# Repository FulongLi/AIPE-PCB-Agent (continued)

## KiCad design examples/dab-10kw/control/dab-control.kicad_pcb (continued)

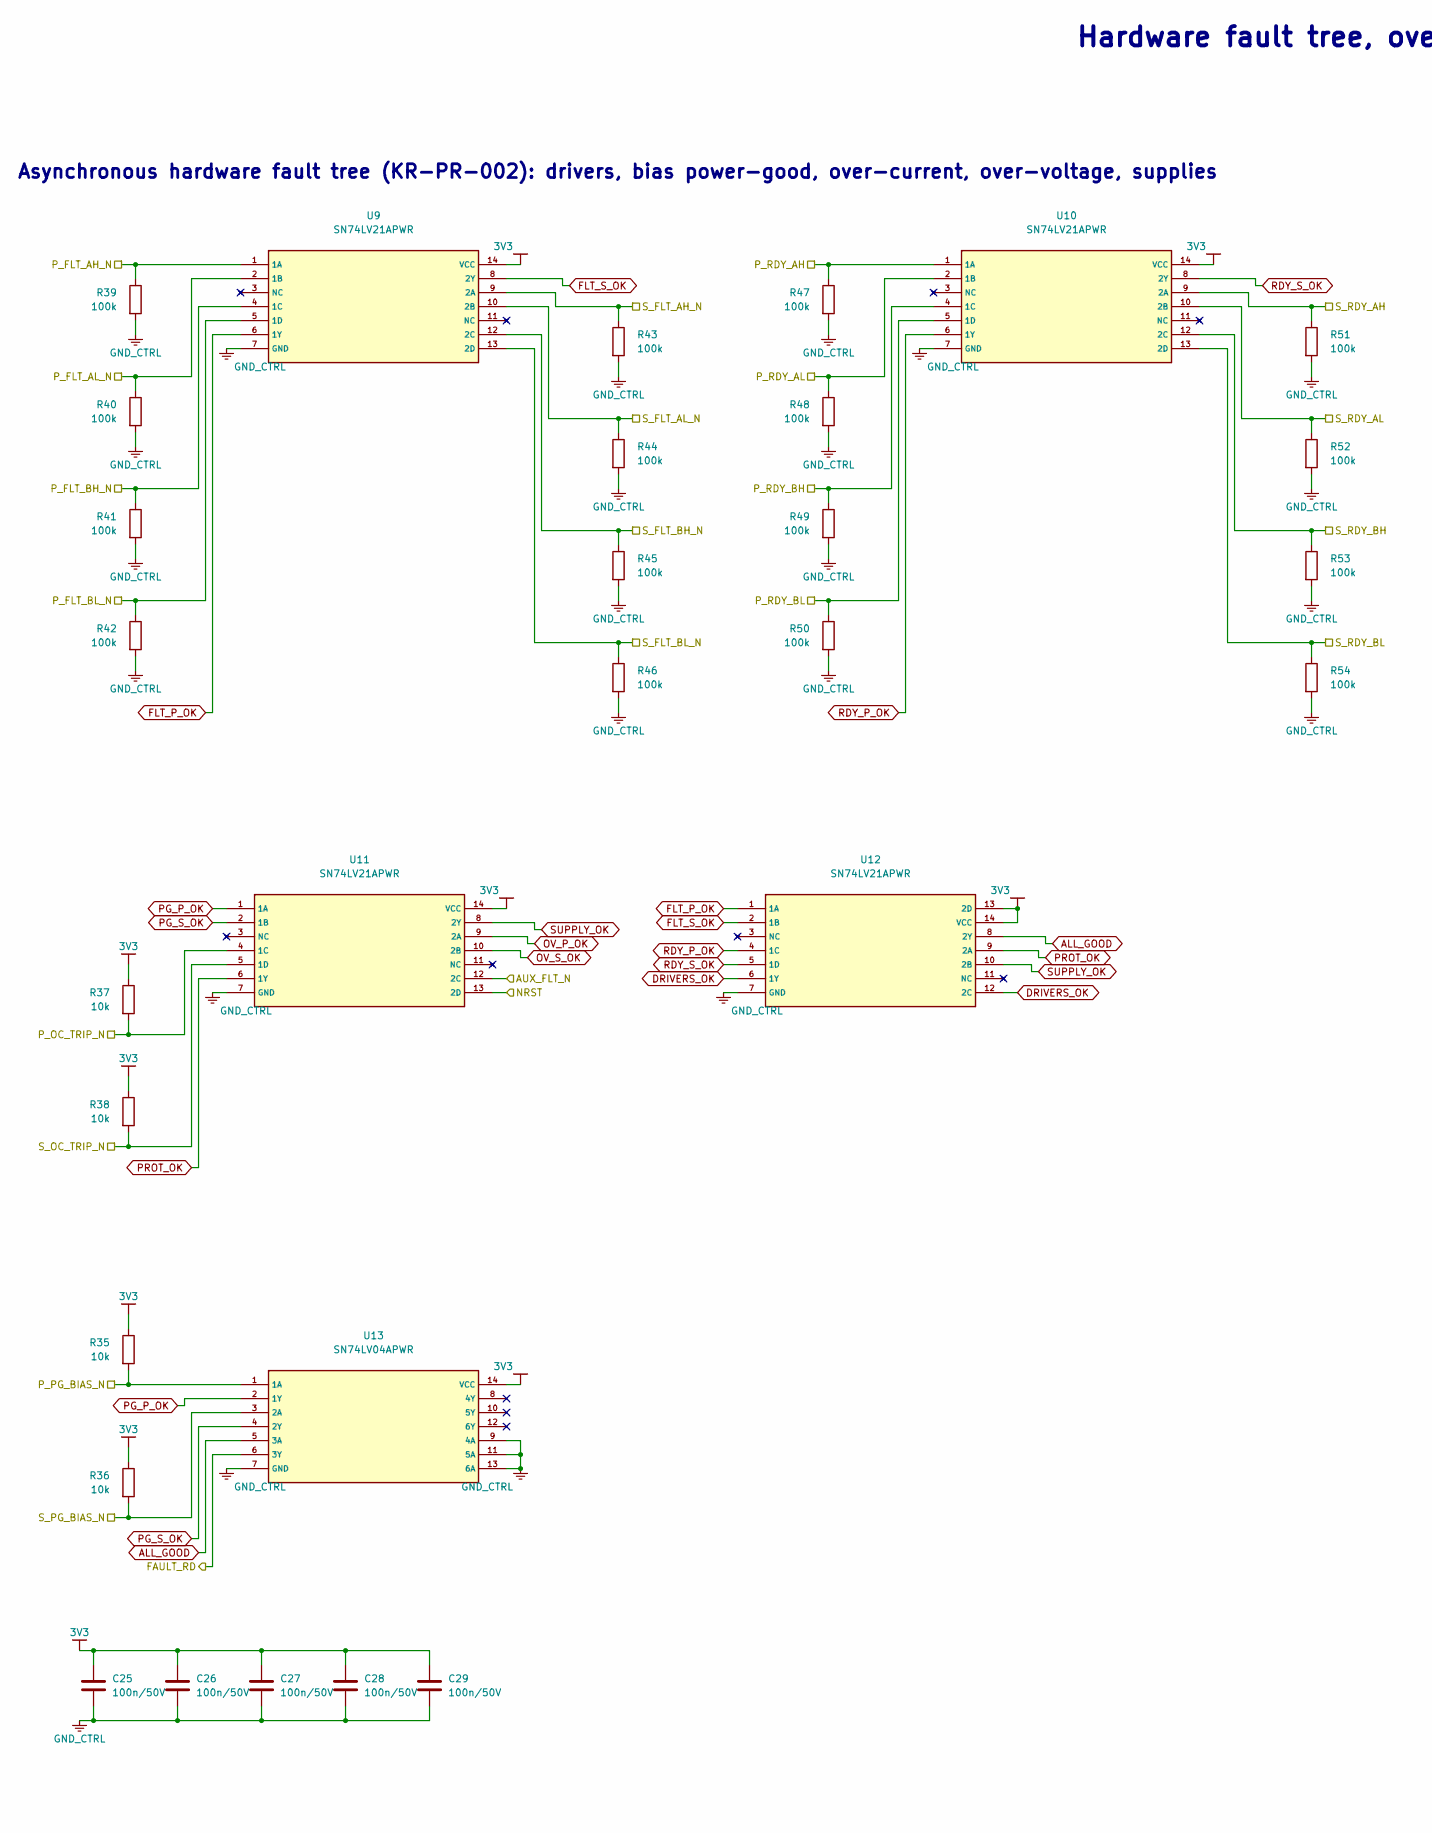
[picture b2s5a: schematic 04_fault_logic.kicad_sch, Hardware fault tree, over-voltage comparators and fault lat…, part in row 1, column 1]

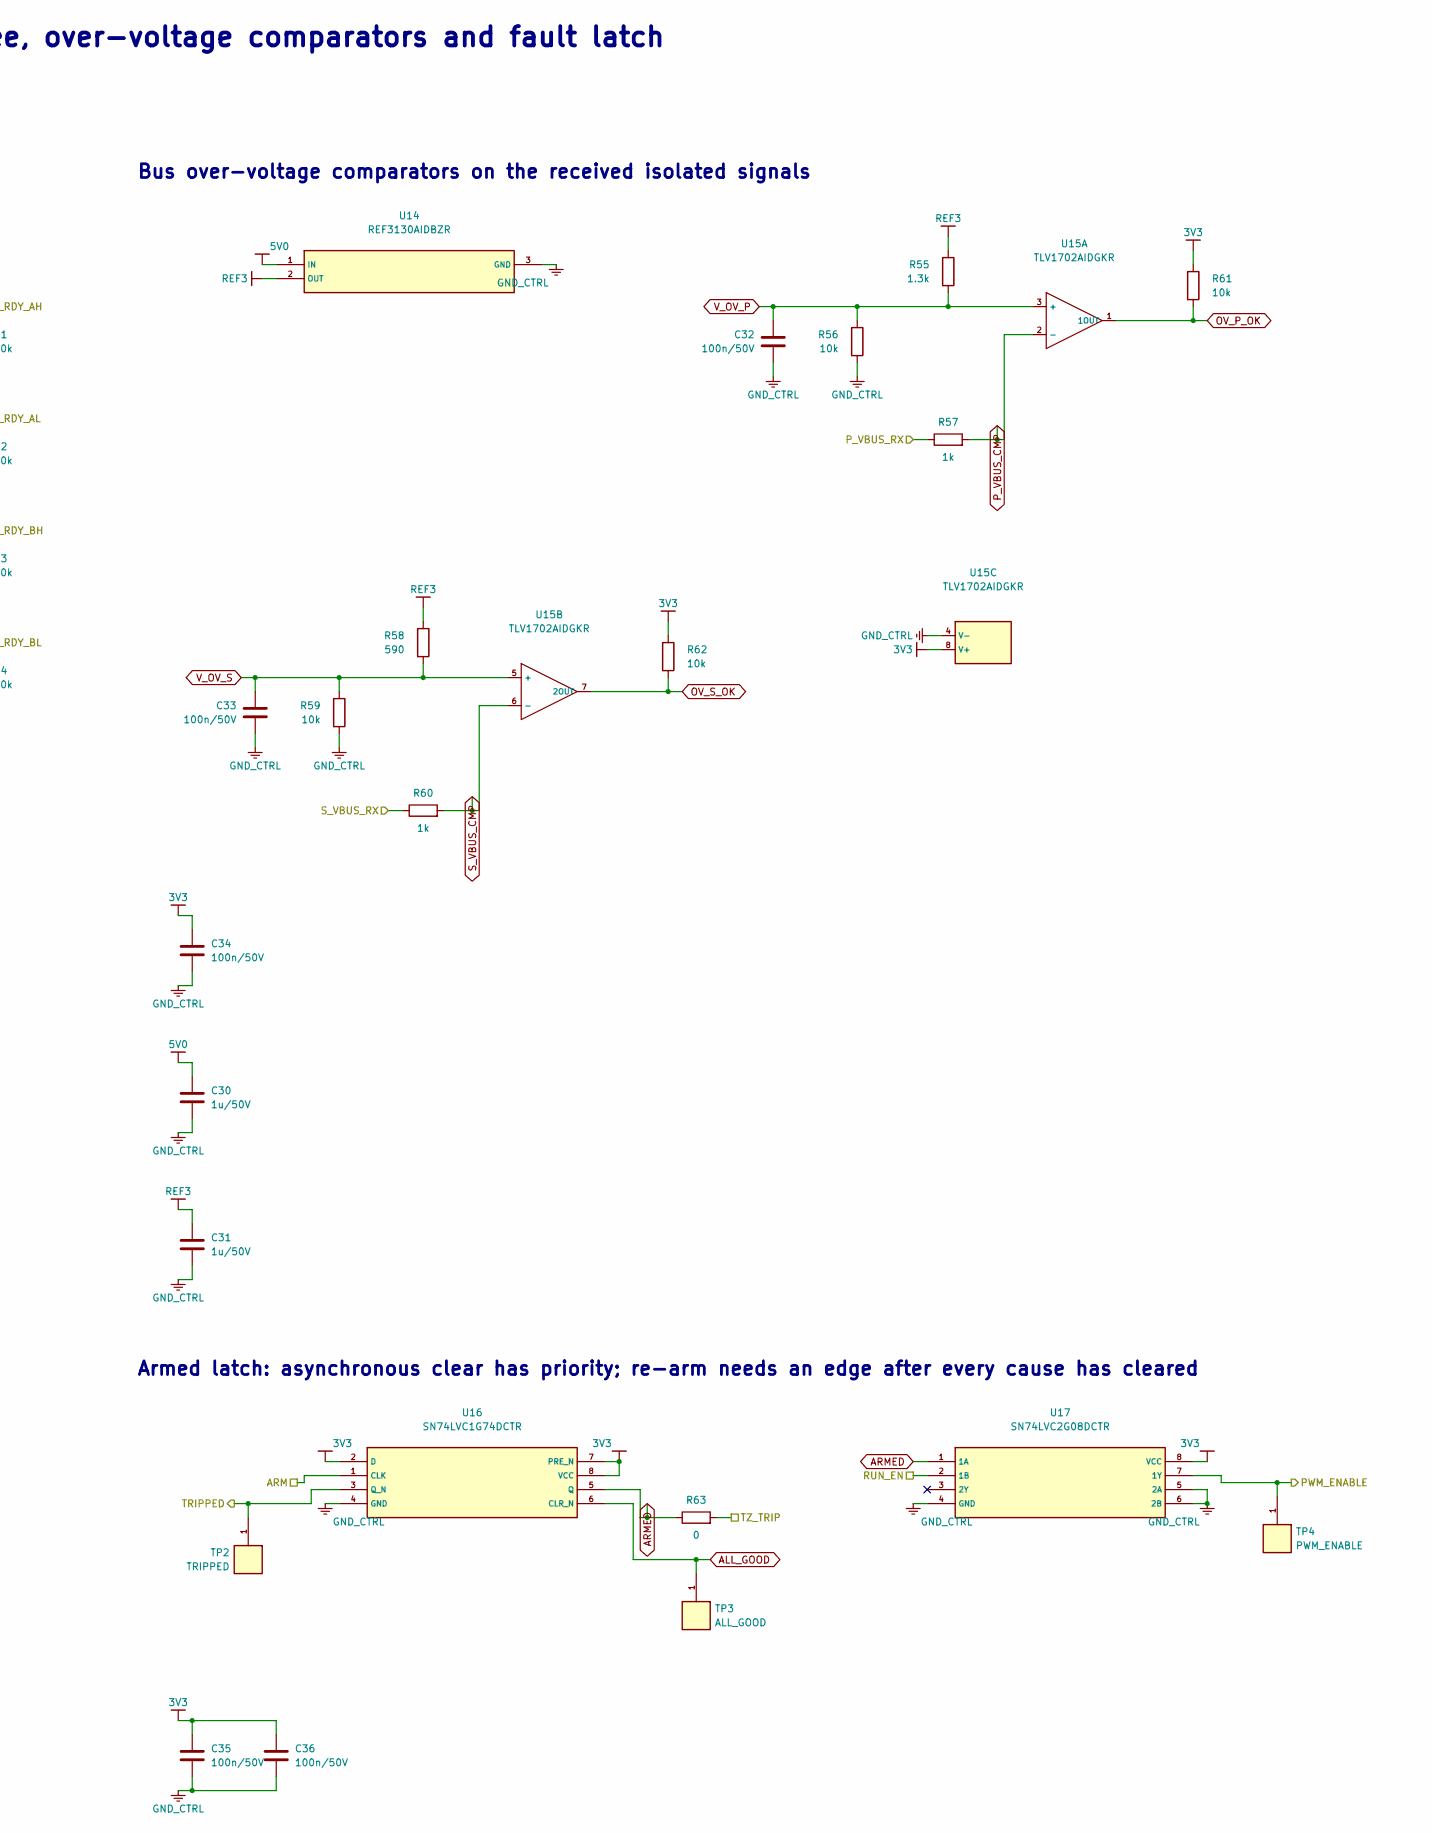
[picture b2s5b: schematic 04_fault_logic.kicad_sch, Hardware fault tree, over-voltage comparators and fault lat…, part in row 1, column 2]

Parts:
C25, C26, C27, C28, C29, C32, C33, C34, C35, C36: 100n/50V; C_0603_1608Metric
C30, C31: 1u/50V; C_0805_2012Metric
R35, R36, R37, R38, R56, R59, R61, R62: 10k; R_0603_1608Metric
R39, R40, R41, R42, R43, R44, R45, R46, R47, R48, R49, R50, R51, R52, R53, R54: 100k; R_0603_1608Metric
R55: 1.3k; R_0603_1608Metric
R57, R60: 1k; R_0603_1608Metric
R58: 590; R_0603_1608Metric
R63: 0; R_0603_1608Metric
TP2: TRIPPED; TestPoint_Pad_D1.0mm
TP3: ALL_GOOD; TestPoint_Pad_D1.0mm
TP4: PWM_ENABLE; TestPoint_Pad_D1.0mm
U9, U10, U11, U12: SN74LV21APWR; TSSOP-14_4.4x5mm_P0.65mm
U13: SN74LV04APWR; TSSOP-14_4.4x5mm_P0.65mm
U14: REF3130AIDBZR; SOT-23
U15: TLV1702AIDGKR; DAB_DGK8
U16: SN74LVC1G74DCTR; SSOP-8_2.95x2.8mm_P0.65mm
U17: SN74LVC2G08DCTR; SSOP-8_2.95x2.8mm_P0.65mm

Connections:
3V3: C25.1, C26.1, C27.1, C28.1, C29.1, C34.1, C35.1, C36.1, R35.1, R36.1, R37.1, R38.1, R61.1, R62.1, U9.14 (VCC), U10.14 (VCC), U11.14 (VCC), U12.13 (2D), U12.14 (VCC), U13.14 (VCC), U15.8 (V+), U16.2 (D), U16.7 (PRE_N), U16.8 (VCC), U17.8 (VCC); also elsewhere on the board
5V0: C30.1, U14.1 (IN); also elsewhere on the board
ALL_GOOD: TP3.1, U12.8 (2Y), U13.5 (3A), U16.6 (CLR_N)
ARM: U16.1 (CLK); also elsewhere on the board
ARMED: R63.1, U16.5 (Q), U17.1 (1A)
AUX_FLT_N: U11.12 (2C); also elsewhere on the board
DRIVERS_OK: U12.6 (1Y), U12.12 (2C)
FAULT_RD: U13.6 (3Y); also elsewhere on the board
FLT_P_OK: U9.6 (1Y), U12.1 (1A)
FLT_S_OK: U9.8 (2Y), U12.2 (1B)
GND_CTRL: C25.2, C26.2, C27.2, C28.2, C29.2, C30.2, C31.2, C32.2, C33.2, C34.2, C35.2, C36.2, R39.2, R40.2, R41.2, R42.2, R43.2, R44.2, R45.2, R46.2, R47.2, R48.2, R49.2, R50.2, R51.2, R52.2, R53.2, R54.2, R56.2, R59.2, U9.7 (GND), U10.7 (GND), U11.7 (GND), U12.7 (GND), U13.7 (GND), U13.9 (4A), U13.11 (5A), U13.13 (6A), U14.3 (GND), U15.4 (V-), U16.4 (GND), U17.4 (GND), U17.5 (2A), U17.6 (2B); also elsewhere on the board
NRST: U11.13 (2D); also elsewhere on the board
OV_P_OK: R61.2, U11.9 (2A), U15.1 (1OUT)
OV_S_OK: R62.2, U11.10 (2B), U15.7 (2OUT)
PG_P_OK: U11.1 (1A), U13.2 (1Y)
PG_S_OK: U11.2 (1B), U13.4 (2Y)
PROT_OK: U11.6 (1Y), U12.9 (2A)
PWM_ENABLE: TP4.1, U17.7 (1Y); also elsewhere on the board
P_FLT_AH_N: R39.1, U9.1 (1A); also elsewhere on the board
P_FLT_AL_N: R40.1, U9.2 (1B); also elsewhere on the board
P_FLT_BH_N: R41.1, U9.4 (1C); also elsewhere on the board
P_FLT_BL_N: R42.1, U9.5 (1D); also elsewhere on the board
P_OC_TRIP_N: R37.2, U11.4 (1C); also elsewhere on the board
P_PG_BIAS_N: R35.2, U13.1 (1A); also elsewhere on the board
P_RDY_AH: R47.1, U10.1 (1A); also elsewhere on the board
P_RDY_AL: R48.1, U10.2 (1B); also elsewhere on the board
P_RDY_BH: R49.1, U10.4 (1C); also elsewhere on the board
P_RDY_BL: R50.1, U10.5 (1D); also elsewhere on the board
P_VBUS_CMP: R57.2, U15.2 (-)
P_VBUS_RX: R57.1; also elsewhere on the board
RDY_P_OK: U10.6 (1Y), U12.4 (1C)
RDY_S_OK: U10.8 (2Y), U12.5 (1D)
REF3: C31.1, R55.1, R58.1, U14.2 (OUT)
RUN_EN: U17.2 (1B); also elsewhere on the board
SUPPLY_OK: U11.8 (2Y), U12.10 (2B)
S_FLT_AH_N: R43.1, U9.9 (2A); also elsewhere on the board
S_FLT_AL_N: R44.1, U9.10 (2B); also elsewhere on the board
S_FLT_BH_N: R45.1, U9.12 (2C); also elsewhere on the board
S_FLT_BL_N: R46.1, U9.13 (2D); also elsewhere on the board
S_OC_TRIP_N: R38.2, U11.5 (1D); also elsewhere on the board
S_PG_BIAS_N: R36.2, U13.3 (2A); also elsewhere on the board
S_RDY_AH: R51.1, U10.9 (2A); also elsewhere on the board
S_RDY_AL: R52.1, U10.10 (2B); also elsewhere on the board
S_RDY_BH: R53.1, U10.12 (2C); also elsewhere on the board
S_RDY_BL: R54.1, U10.13 (2D); also elsewhere on the board
S_VBUS_CMP: R60.2, U15.6 (-)
S_VBUS_RX: R60.1; also elsewhere on the board
TRIPPED: TP2.1, U16.3 (Q_N); also elsewhere on the board
TZ_TRIP: R63.2; also elsewhere on the board
V_OV_P: C32.1, R55.2, R56.1, U15.3 (+)
V_OV_S: C33.1, R58.2, R59.1, U15.5 (+)

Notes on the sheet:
Hardware fault tree, over-voltage comparators and fault latch
Asynchronous hardware fault tree (KR-PR-002): drivers, bias power-good, over-current, over-voltage, supplies
Bus over-voltage comparators on the received isolated signals
Armed latch: asynchronous clear has priority; re-arm needs an edge after every cause has cleared

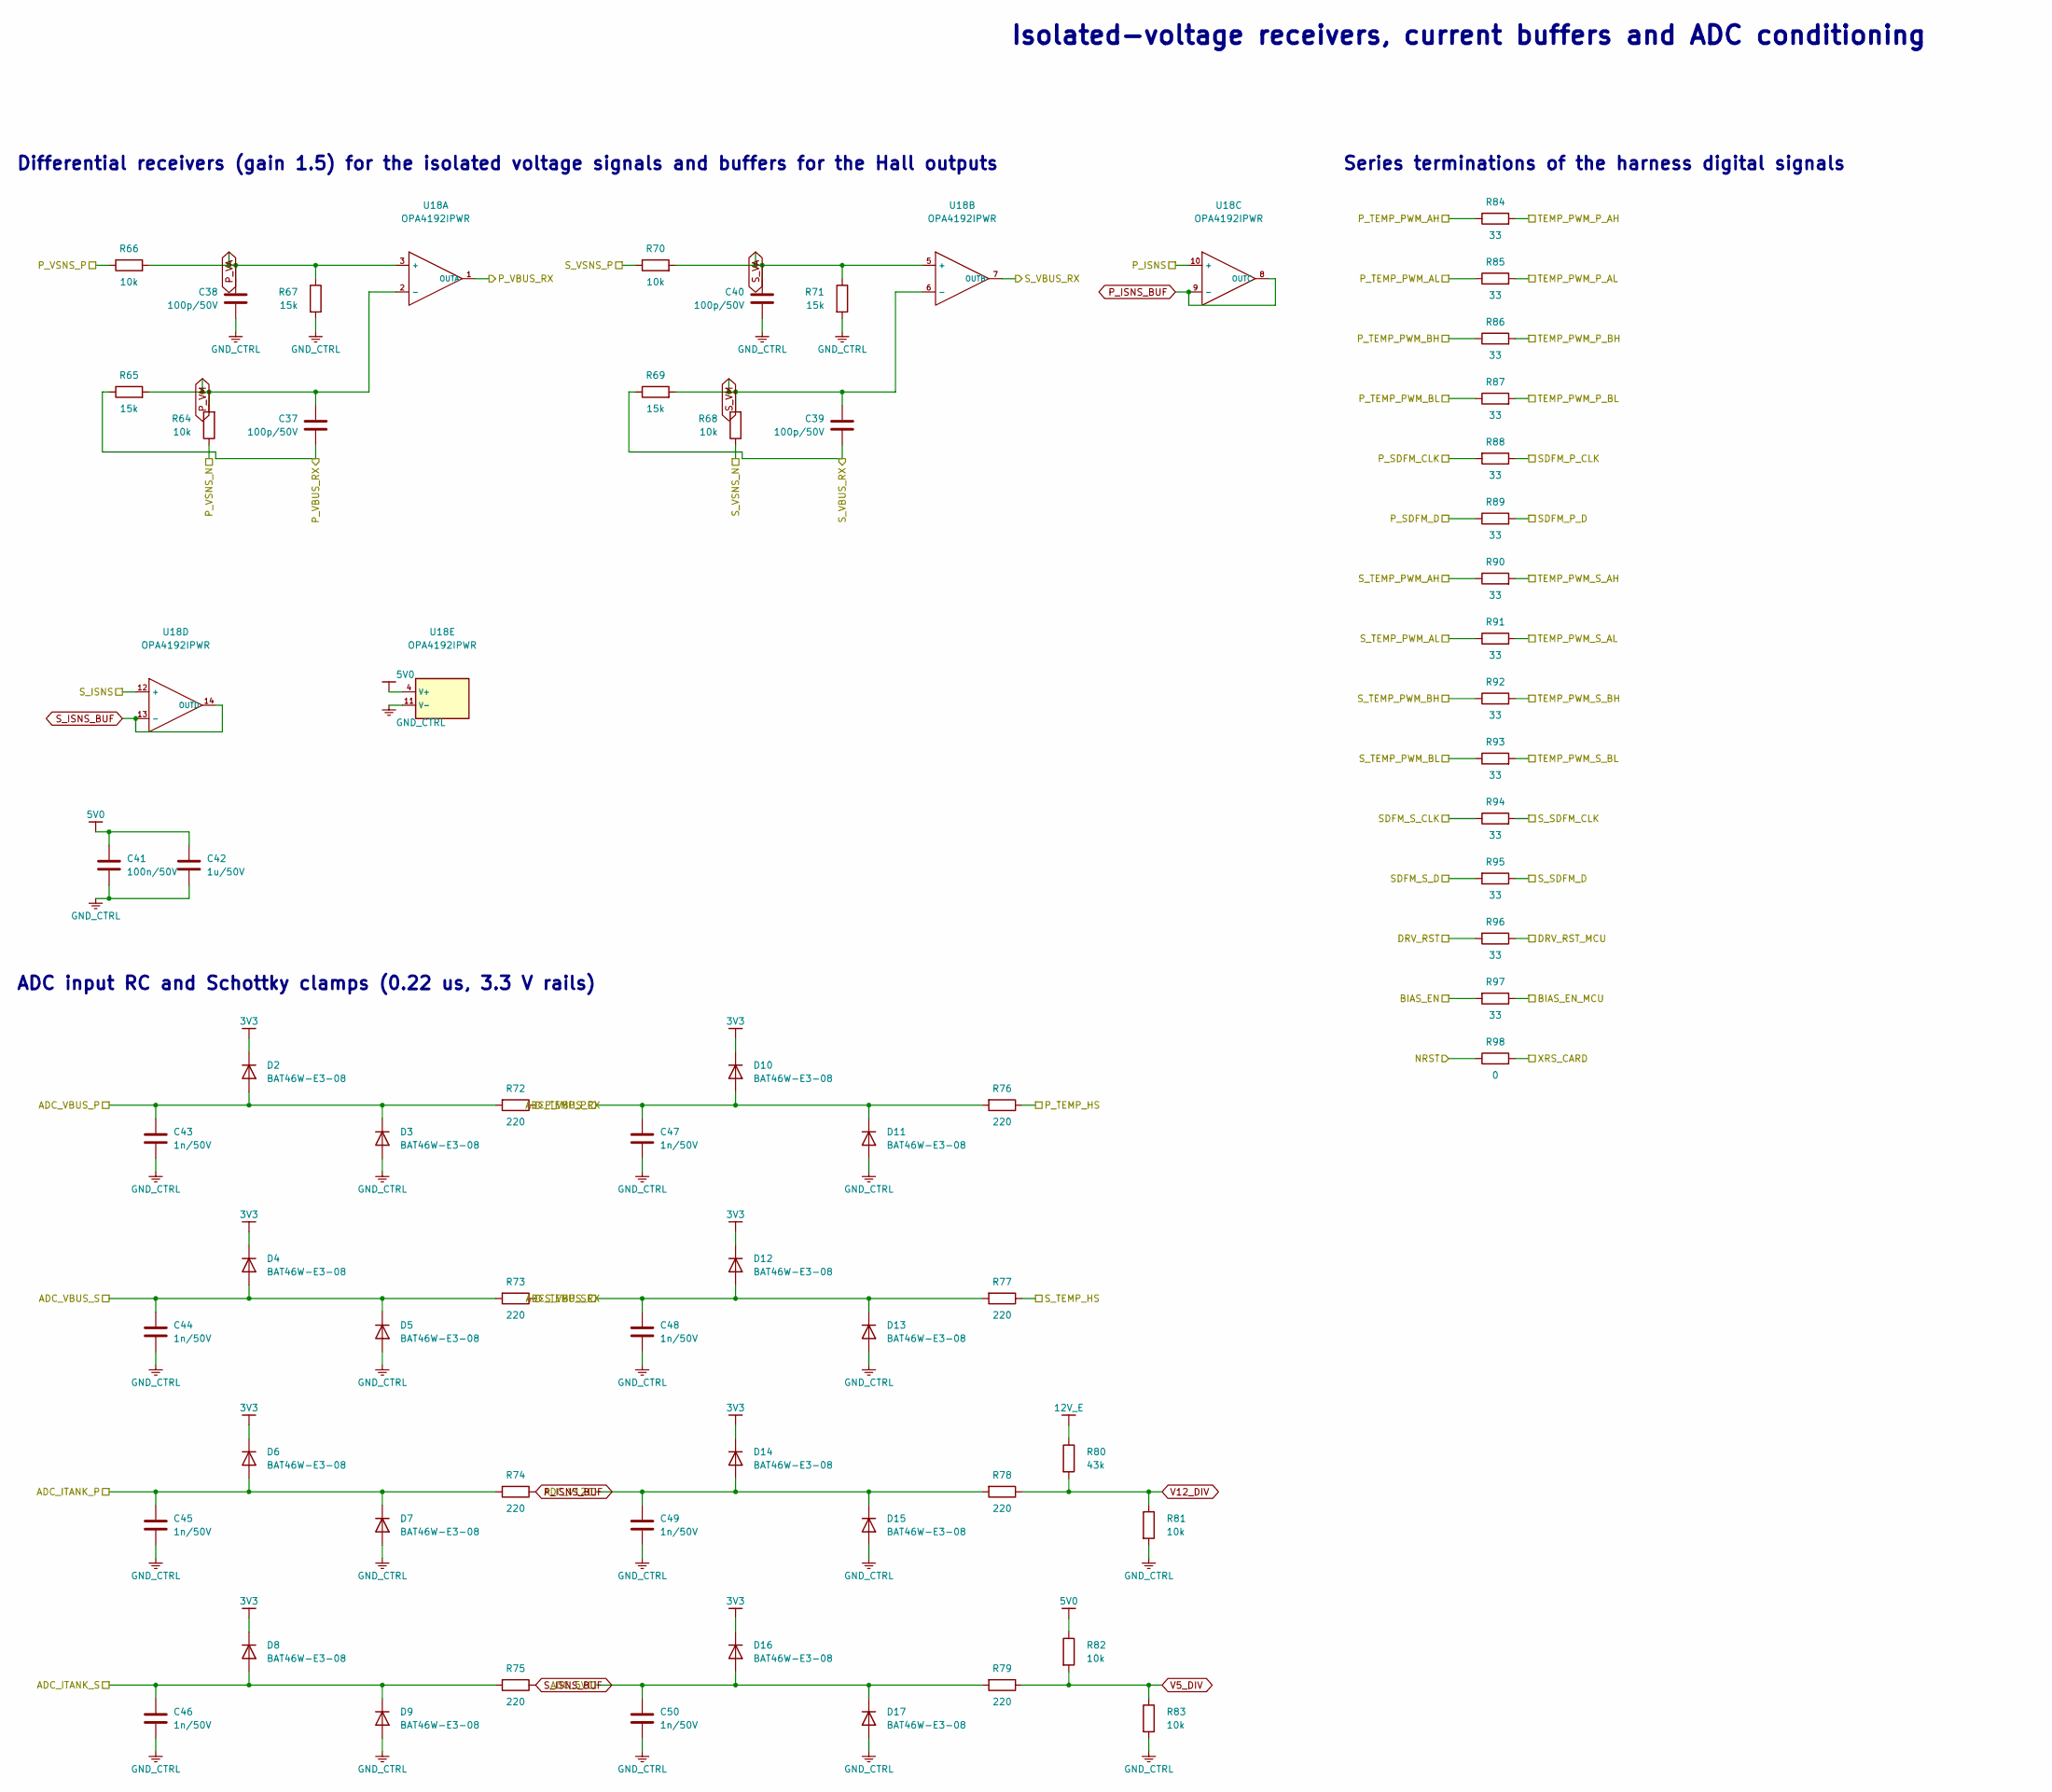
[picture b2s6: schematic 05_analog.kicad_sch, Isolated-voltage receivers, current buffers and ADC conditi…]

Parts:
C37, C38, C39, C40: 100p/50V; C_0603_1608Metric
C41: 100n/50V; C_0603_1608Metric
C42: 1u/50V; C_0805_2012Metric
C43, C44, C45, C46, C47, C48, C49, C50: 1n/50V; C_0603_1608Metric
D2, D3, D4, D5, D6, D7, D8, D9, D10, D11, D12, D13, D14, D15, D16, D17: BAT46W-E3-08; D_SOD-123
R64, R66, R68, R70, R81, R82, R83: 10k; R_0603_1608Metric
R65, R67, R69, R71: 15k; R_0603_1608Metric
R72, R73, R74, R75, R76, R77, R78, R79: 220; R_0603_1608Metric
R80: 43k; R_0603_1608Metric
R84, R85, R86, R87, R88, R89, R90, R91, R92, R93, R94, R95, R96, R97: 33; R_0603_1608Metric
R98: 0; R_0603_1608Metric
U18: OPA4192IPWR; TSSOP-14_4.4x5mm_P0.65mm

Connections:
3V3: D2.1 (K), D4.1 (K), D6.1 (K), D8.1 (K), D10.1 (K), D12.1 (K), D14.1 (K), D16.1 (K); also elsewhere on the board
5V0: C41.1, C42.1, R82.1, U18.4 (V+); also elsewhere on the board
12V_E: R80.1; also elsewhere on the board
ADC_5V: C50.1, D16.2 (A), D17.1 (K), R79.2; also elsewhere on the board
ADC_ITANK_P: C45.1, D6.2 (A), D7.1 (K), R74.2; also elsewhere on the board
ADC_ITANK_S: C46.1, D8.2 (A), D9.1 (K), R75.2; also elsewhere on the board
ADC_TEMP_P: C47.1, D10.2 (A), D11.1 (K), R76.2; also elsewhere on the board
ADC_TEMP_S: C48.1, D12.2 (A), D13.1 (K), R77.2; also elsewhere on the board
ADC_V12: C49.1, D14.2 (A), D15.1 (K), R78.2; also elsewhere on the board
ADC_VBUS_P: C43.1, D2.2 (A), D3.1 (K), R72.2; also elsewhere on the board
ADC_VBUS_S: C44.1, D4.2 (A), D5.1 (K), R73.2; also elsewhere on the board
BIAS_EN: R97.2; also elsewhere on the board
BIAS_EN_MCU: R97.1; also elsewhere on the board
DRV_RST: R96.2; also elsewhere on the board
DRV_RST_MCU: R96.1; also elsewhere on the board
GND_CTRL: C38.2, C40.2, C41.2, C42.2, C43.2, C44.2, C45.2, C46.2, C47.2, C48.2, C49.2, C50.2, D3.2 (A), D5.2 (A), D7.2 (A), D9.2 (A), D11.2 (A), D13.2 (A), D15.2 (A), D17.2 (A), R67.2, R71.2, R81.2, R83.2, U18.11 (V-); also elsewhere on the board
NRST: R98.1; also elsewhere on the board
P_ISNS: U18.10 (+); also elsewhere on the board
P_ISNS_BUF: R74.1, U18.8 (OUTC), U18.9 (-)
P_SDFM_CLK: R88.2; also elsewhere on the board
P_SDFM_D: R89.1; also elsewhere on the board
P_TEMP_HS: R76.1; also elsewhere on the board
P_TEMP_PWM_AH: R84.1; also elsewhere on the board
P_TEMP_PWM_AL: R85.1; also elsewhere on the board
P_TEMP_PWM_BH: R86.1; also elsewhere on the board
P_TEMP_PWM_BL: R87.1; also elsewhere on the board
P_VA: C38.1, R66.2, R67.1, U18.3 (+)
P_VBUS_RX: C37.1, R65.1, R72.1, U18.1 (OUTA); also elsewhere on the board
P_VM: C37.2, R64.2, R65.2, U18.2 (-)
P_VSNS_N: R64.1; also elsewhere on the board
P_VSNS_P: R66.1; also elsewhere on the board
SDFM_P_CLK: R88.1; also elsewhere on the board
SDFM_P_D: R89.2; also elsewhere on the board
SDFM_S_CLK: R94.1; also elsewhere on the board
SDFM_S_D: R95.2; also elsewhere on the board
S_ISNS: U18.12 (+); also elsewhere on the board
S_ISNS_BUF: R75.1, U18.13 (-), U18.14 (OUTD)
S_SDFM_CLK: R94.2; also elsewhere on the board
S_SDFM_D: R95.1; also elsewhere on the board
S_TEMP_HS: R77.1; also elsewhere on the board
S_TEMP_PWM_AH: R90.1; also elsewhere on the board
S_TEMP_PWM_AL: R91.1; also elsewhere on the board
S_TEMP_PWM_BH: R92.1; also elsewhere on the board
S_TEMP_PWM_BL: R93.1; also elsewhere on the board
S_VA: C40.1, R70.2, R71.1, U18.5 (+)
S_VBUS_RX: C39.1, R69.1, R73.1, U18.7 (OUTB); also elsewhere on the board
S_VM: C39.2, R68.2, R69.2, U18.6 (-)
S_VSNS_N: R68.1; also elsewhere on the board
S_VSNS_P: R70.1; also elsewhere on the board
TEMP_PWM_P_AH: R84.2; also elsewhere on the board
TEMP_PWM_P_AL: R85.2; also elsewhere on the board
TEMP_PWM_P_BH: R86.2; also elsewhere on the board
TEMP_PWM_P_BL: R87.2; also elsewhere on the board
TEMP_PWM_S_AH: R90.2; also elsewhere on the board
TEMP_PWM_S_AL: R91.2; also elsewhere on the board
TEMP_PWM_S_BH: R92.2; also elsewhere on the board
TEMP_PWM_S_BL: R93.2; also elsewhere on the board
V5_DIV: R79.1, R82.2, R83.1
V12_DIV: R78.1, R80.2, R81.1
XRS_CARD: R98.2; also elsewhere on the board

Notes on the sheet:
Isolated-voltage receivers, current buffers and ADC conditioning
Differential receivers (gain 1.5) for the isolated voltage signals and buffers for the Hall outputs
ADC input RC and Schottky clamps (0.22 us, 3.3 V rails)
Series terminations of the harness digital signals

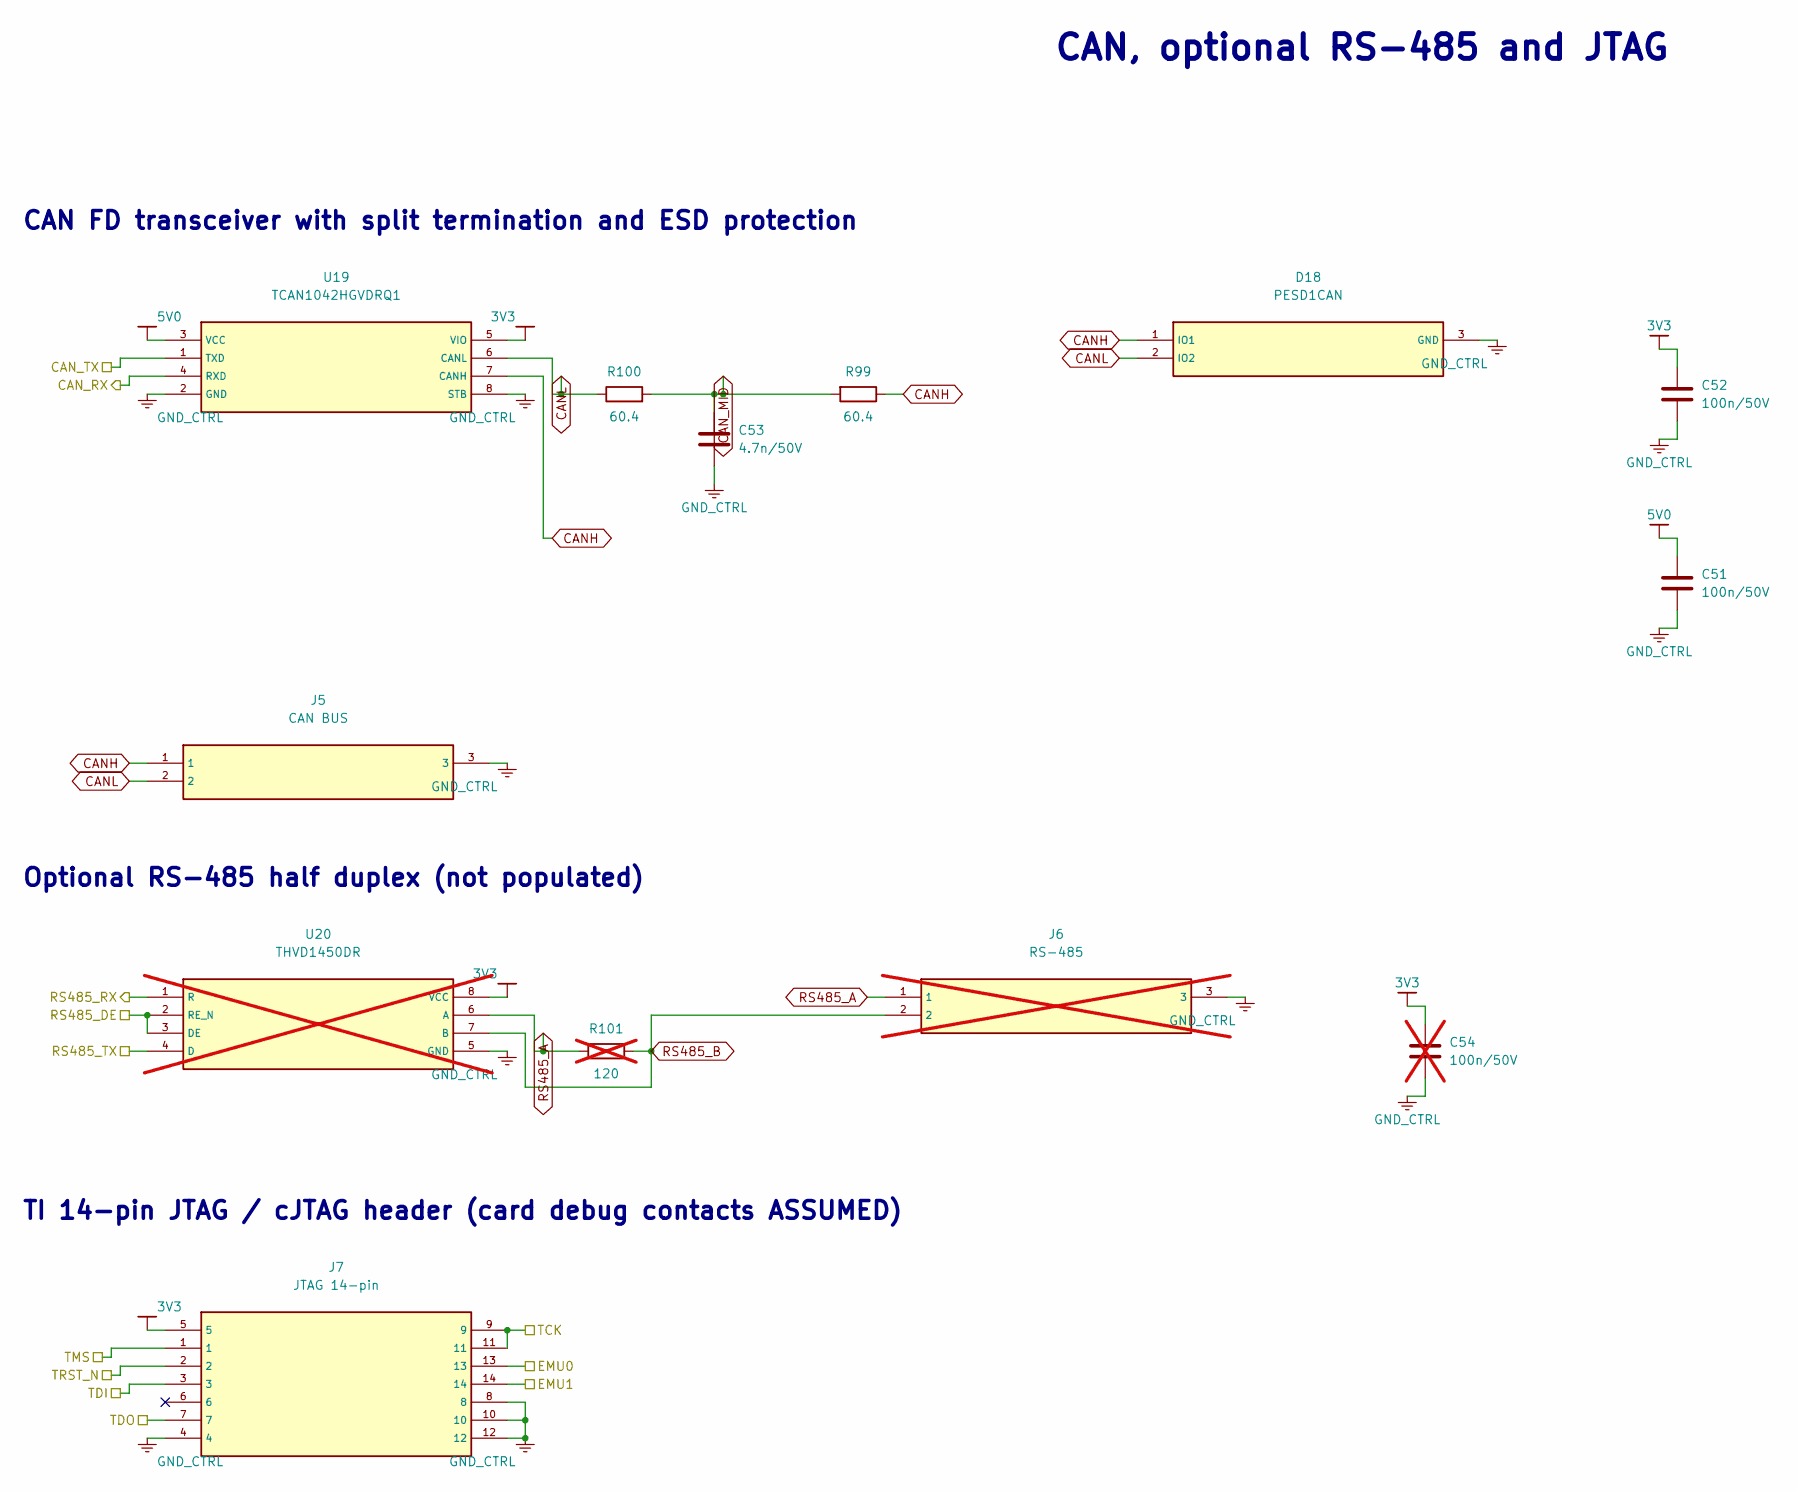
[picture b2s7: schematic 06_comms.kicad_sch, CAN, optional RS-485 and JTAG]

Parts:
C51, C52: 100n/50V; C_0603_1608Metric
C53: 4.7n/50V; C_0603_1608Metric
C54: 100n/50V; C_0603_1608Metric; not fitted
D18: PESD1CAN; SOT-23
J5: CAN BUS; PhoenixContact_MC_1,5_3-G-3.81_1x03_P3.81mm_Horizontal
J6: RS-485; PhoenixContact_MC_1,5_3-G-3.81_1x03_P3.81mm_Horizontal; not fitted
J7: JTAG 14-pin; PinHeader_2x07_P2.54mm_Vertical
R99, R100: 60.4; R_0603_1608Metric
R101: 120; R_0603_1608Metric; not fitted
U19: TCAN1042HGVDRQ1; SOIC-8_3.9x4.9mm_P1.27mm
U20: THVD1450DR; SOIC-8_3.9x4.9mm_P1.27mm; not fitted

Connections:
3V3: C52.1, C54.1, J7.5, U19.5 (VIO), U20.8 (VCC); also elsewhere on the board
5V0: C51.1, U19.3 (VCC); also elsewhere on the board
CANH: D18.1 (IO1), J5.1, R99.1, U19.7 (CANH)
CANL: D18.2 (IO2), J5.2, R100.1, U19.6 (CANL)
CAN_MID: C53.1, R99.2, R100.2
CAN_RX: U19.4 (RXD); also elsewhere on the board
CAN_TX: U19.1 (TXD); also elsewhere on the board
EMU0: J7.13; also elsewhere on the board
EMU1: J7.14; also elsewhere on the board
GND_CTRL: C51.2, C52.2, C53.2, C54.2, D18.3 (GND), J5.3, J6.3, J7.4, J7.8, J7.10, J7.12, U19.2 (GND), U19.8 (STB), U20.5 (GND); also elsewhere on the board
RS485_A: J6.1, R101.1, U20.6 (A)
RS485_B: J6.2, R101.2, U20.7 (B)
RS485_DE: U20.2 (RE_N), U20.3 (DE); also elsewhere on the board
RS485_RX: U20.1 (R); also elsewhere on the board
RS485_TX: U20.4 (D); also elsewhere on the board
TCK: J7.9, J7.11; also elsewhere on the board
TDI: J7.3; also elsewhere on the board
TDO: J7.7; also elsewhere on the board
TMS: J7.1; also elsewhere on the board
TRST_N: J7.2; also elsewhere on the board

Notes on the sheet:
CAN, optional RS-485 and JTAG
CAN FD transceiver with split termination and ESD protection
Optional RS-485 half duplex (not populated)
TI 14-pin JTAG / cJTAG header (card debug contacts ASSUMED)
